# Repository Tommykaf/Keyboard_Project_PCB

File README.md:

# keyboard_project

A Keyboard pcb modeled by @tommykark03, @thunde7, @wifi and @staveyal

## Parts

- MCU: ATMEGA32U4
- USB: TYPE-C-31-M-12
- DIODE: 1N4148W SOD-123

RESISTORS:
- 22 OHM - 0603WAF220JT5E
- 10k OHM - 0603WAF1002T5E
- 5.1K OHM - 0603WAF5101T5E

CAPACITORS:
- 1uF - CL10A105KB8NNNC
- 10uF - CL10A106KP8NNNC 
- 0.1uF (100pF) - CL10C101JB8NNNC

Quartz:
- Yangxing Tech X252016MLD4SC

Tactile reset:
- PANASONIC EVPBB4A9B000

Ferrite Bead:
- GZ1608D601TF

## layout

## MORE SCREENSHOTS

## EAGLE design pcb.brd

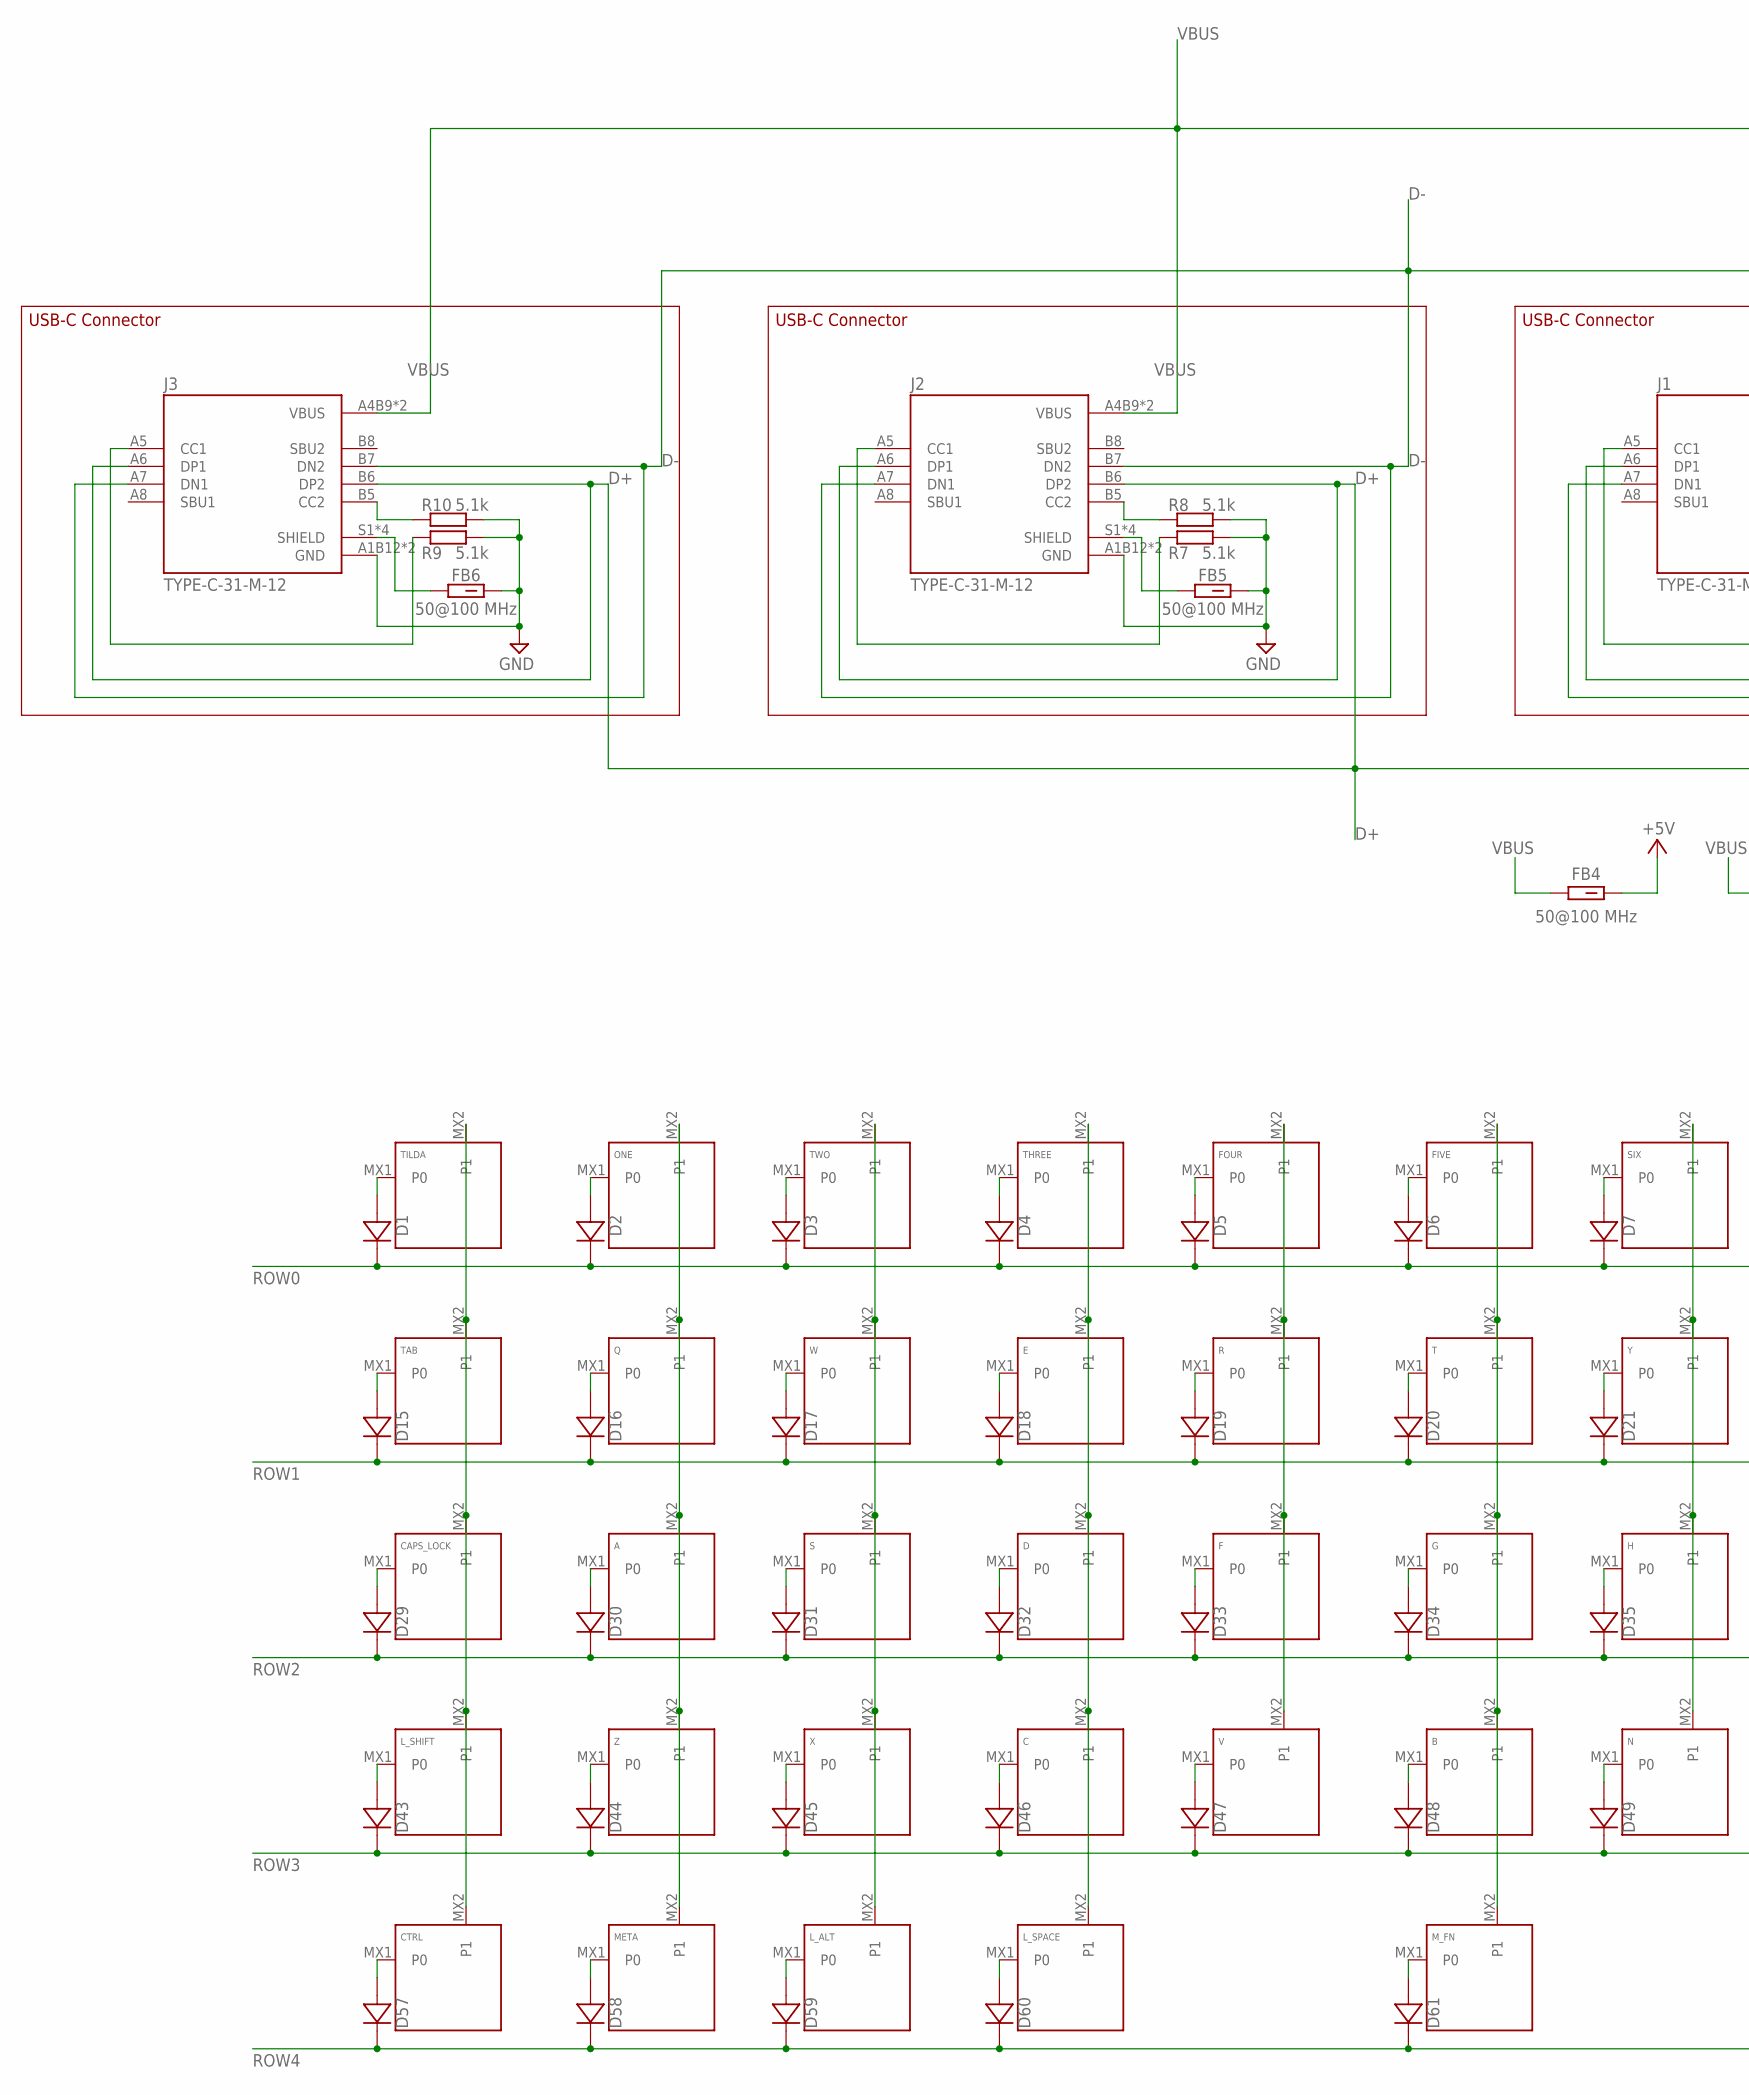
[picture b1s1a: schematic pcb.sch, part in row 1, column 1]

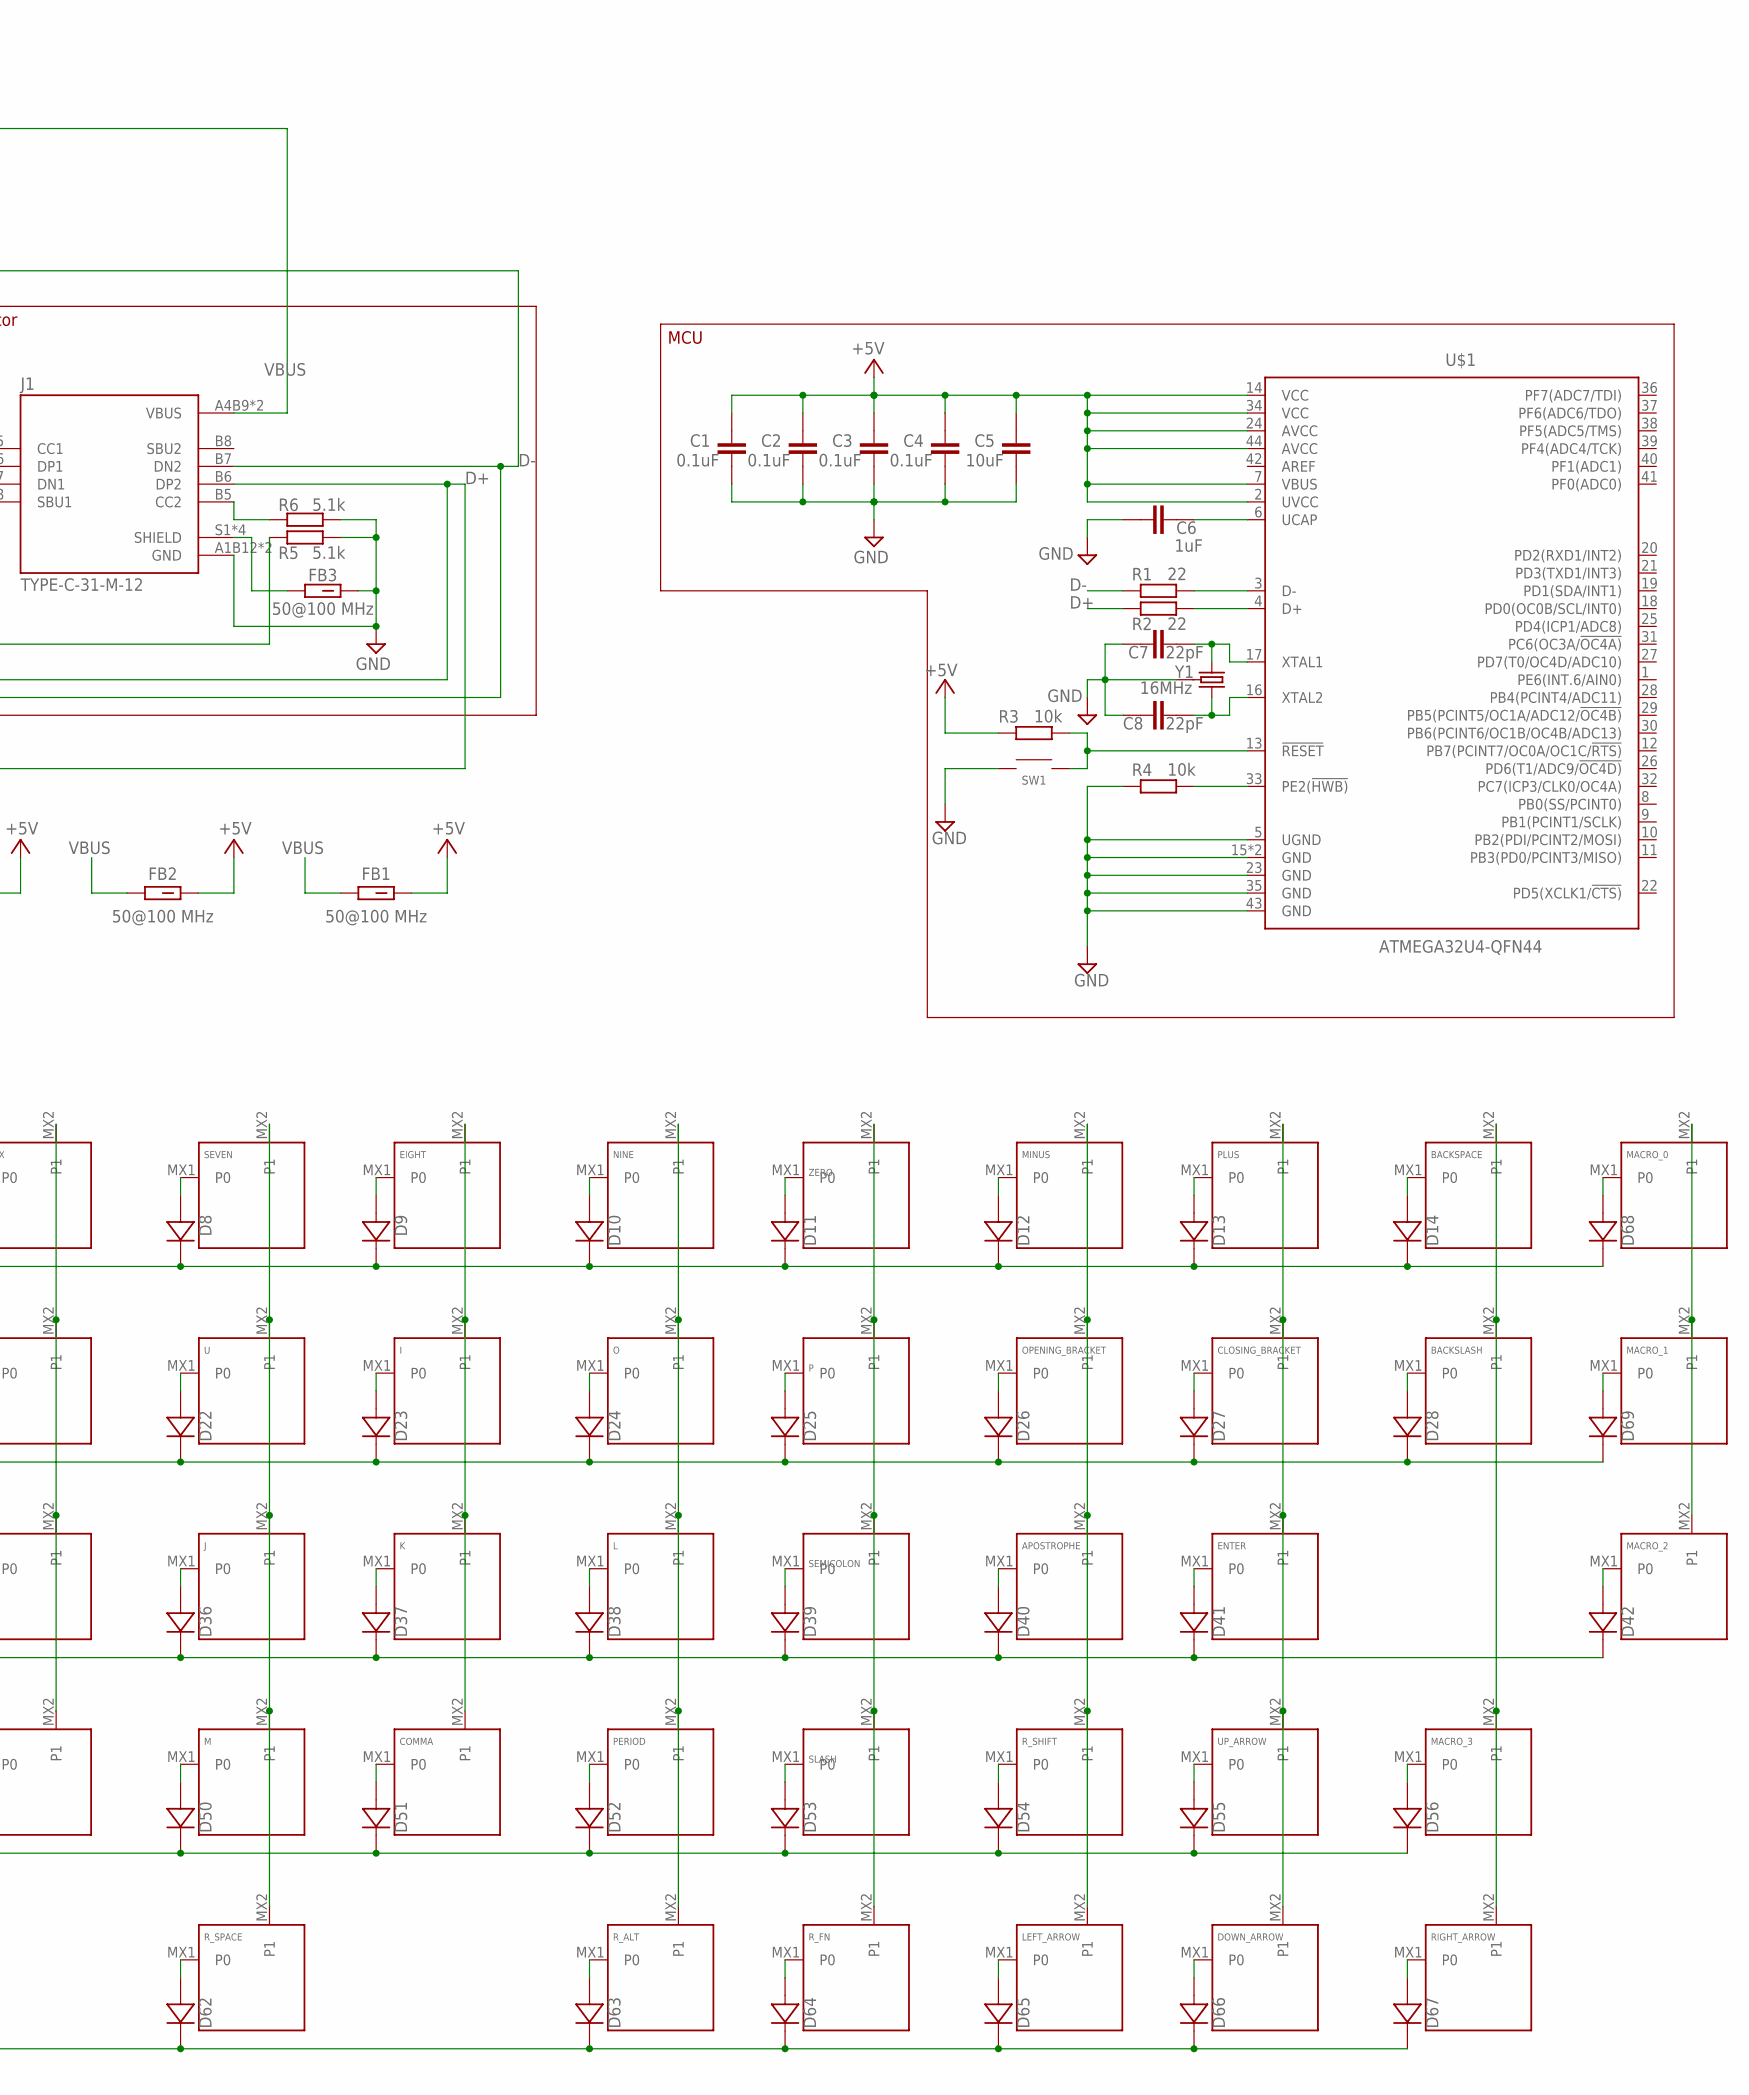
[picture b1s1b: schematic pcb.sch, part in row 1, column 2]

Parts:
A: KEYSWITCH-PLAIN-MXHSPCB-1U; MXHSPCB-1U
APOSTROPHE: KEYSWITCH-PLAIN-MXHSPCB-1U; MXHSPCB-1U
B: KEYSWITCH-PLAIN-MXHSPCB-1U; MXHSPCB-1U
BACKSLASH: KEYSWITCH-PLAIN-MXHSPCB-1U; MXHSPCB-1U
BACKSPACE: KEYSWITCH-PLAIN-MXHSPCB-2U; MXHSPCB-2U
C: KEYSWITCH-PLAIN-MXHSPCB-1U; MXHSPCB-1U
C1, C2, C3, C4: 0.1uF; C0603
C5: 10uF; C0603
C6: 1uF; C0603
C7, C8: 22pF; C0603
CAPS_LOCK: KEYSWITCH-PLAIN-MXHSPCB-1U; MXHSPCB-1U
CLOSING_BRACKET: KEYSWITCH-PLAIN-MXHSPCB-1U; MXHSPCB-1U
COMMA: KEYSWITCH-PLAIN-MXHSPCB-1U; MXHSPCB-1U
CTRL: KEYSWITCH-PLAIN-MXHSPCB-1U; MXHSPCB-1U
D: KEYSWITCH-PLAIN-MXHSPCB-1U; MXHSPCB-1U
D1, D2, D3, D4, D5, D6, D7, D8, D9, D10, D11, D12, D13, D14, D15, D16, D17, D18, D19, D20, D21, D22, D23, D24, D25, D26, D27, D28, D29, D30, D31, D32, D33, D34, D35, D36, D37, D38, D39, D40, D41, D42, D43, D44, D45, D46, D47, D48, D49, D50, D51, D52, D53, D54, D55, D56, D57, D58, D59, D60, D61, D62, D63, D64, D65, D66, D67, D68, D69: DIODE-SOD-123; SOD-123
DOWN_ARROW: KEYSWITCH-PLAIN-MXHSPCB-1U; MXHSPCB-1U
E: KEYSWITCH-PLAIN-MXHSPCB-1U; MXHSPCB-1U
EIGHT: KEYSWITCH-PLAIN-MXHSPCB-1U; MXHSPCB-1U
ENTER: KEYSWITCH-PLAIN-MXHSPCB-2U; MXHSPCB-2U
F: KEYSWITCH-PLAIN-MXHSPCB-1U; MXHSPCB-1U
FB1, FB2, FB3, FB4, FB5, FB6: 50@100 MHz; BEADC1608X95N
FIVE: KEYSWITCH-PLAIN-MXHSPCB-1U; MXHSPCB-1U
FOUR: KEYSWITCH-PLAIN-MXHSPCB-1U; MXHSPCB-1U
G: KEYSWITCH-PLAIN-MXHSPCB-1U; MXHSPCB-1U
H: KEYSWITCH-PLAIN-MXHSPCB-1U; MXHSPCB-1U
I: KEYSWITCH-PLAIN-MXHSPCB-1U; MXHSPCB-1U
J: KEYSWITCH-PLAIN-MXHSPCB-1U; MXHSPCB-1U
J1, J2, J3: TYPE-C-31-M-12; HRO_TYPE-C-31-M-12
K: KEYSWITCH-PLAIN-MXHSPCB-1U; MXHSPCB-1U
L: KEYSWITCH-PLAIN-MXHSPCB-1U; MXHSPCB-1U
LEFT_ARROW: KEYSWITCH-PLAIN-MXHSPCB-1U; MXHSPCB-1U
L_ALT: KEYSWITCH-PLAIN-MXHSPCB-1U; MXHSPCB-1U
L_SHIFT: KEYSWITCH-PLAIN-MXHSPCB-2U; MXHSPCB-2U
L_SPACE: KEYSWITCH-PLAIN-MXHSPCB-2U-FLIPPED; MXHSPCB-2U-FLIPPED
M: KEYSWITCH-PLAIN-MXHSPCB-1U; MXHSPCB-1U
MACRO_0, MACRO_1, MACRO_2, MACRO_3: KEYSWITCH-PLAIN-MXHSPCB-1U; MXHSPCB-1U
META: KEYSWITCH-PLAIN-MXHSPCB-1U; MXHSPCB-1U
MINUS: KEYSWITCH-PLAIN-MXHSPCB-1U; MXHSPCB-1U
M_FN: KEYSWITCH-PLAIN-MXHSPCB-1U; MXHSPCB-1U
N: KEYSWITCH-PLAIN-MXHSPCB-1U; MXHSPCB-1U
NINE: KEYSWITCH-PLAIN-MXHSPCB-1U; MXHSPCB-1U
O: KEYSWITCH-PLAIN-MXHSPCB-1U; MXHSPCB-1U
ONE: KEYSWITCH-PLAIN-MXHSPCB-1U; MXHSPCB-1U
OPENING_BRACKET: KEYSWITCH-PLAIN-MXHSPCB-1U; MXHSPCB-1U
P: KEYSWITCH-PLAIN-MXHSPCB-1U; MXHSPCB-1U
PERIOD: KEYSWITCH-PLAIN-MXHSPCB-1U; MXHSPCB-1U
PLUS: KEYSWITCH-PLAIN-MXHSPCB-1U; MXHSPCB-1U
Q: KEYSWITCH-PLAIN-MXHSPCB-1U; MXHSPCB-1U
R: KEYSWITCH-PLAIN-MXHSPCB-1U; MXHSPCB-1U
R1, R2: 22; R0603
R3, R4: 10k; R0603
R5, R6, R7, R8, R9, R10: 5.1k; R0603
RIGHT_ARROW: KEYSWITCH-PLAIN-MXHSPCB-1U; MXHSPCB-1U
R_ALT: KEYSWITCH-PLAIN-MXHSPCB-1U; MXHSPCB-1U
R_FN: KEYSWITCH-PLAIN-MXHSPCB-1U; MXHSPCB-1U
R_SHIFT: KEYSWITCH-PLAIN-MXHSPCB-1U; MXHSPCB-1U
R_SPACE: KEYSWITCH-PLAIN-MXHSPCB-2U-FLIPPED; MXHSPCB-2U-FLIPPED
S: KEYSWITCH-PLAIN-MXHSPCB-1U; MXHSPCB-1U
SEMICOLON: KEYSWITCH-PLAIN-MXHSPCB-1U; MXHSPCB-1U
SEVEN: KEYSWITCH-PLAIN-MXHSPCB-1U; MXHSPCB-1U
SIX: KEYSWITCH-PLAIN-MXHSPCB-1U; MXHSPCB-1U
SLASH: KEYSWITCH-PLAIN-MXHSPCB-1U; MXHSPCB-1U
SW1: SWITCH-SMD-EVP-BB2A9B00
T: KEYSWITCH-PLAIN-MXHSPCB-1U; MXHSPCB-1U
TAB: KEYSWITCH-PLAIN-MXHSPCB-1U; MXHSPCB-1U
THREE: KEYSWITCH-PLAIN-MXHSPCB-1U; MXHSPCB-1U
TILDA: KEYSWITCH-PLAIN-MXHSPCB-1U; MXHSPCB-1U
TWO: KEYSWITCH-PLAIN-MXHSPCB-1U; MXHSPCB-1U
U: KEYSWITCH-PLAIN-MXHSPCB-1U; MXHSPCB-1U
U$1: ATMEGA32U4-QFN44; QFN-44
UP_ARROW: KEYSWITCH-PLAIN-MXHSPCB-1U; MXHSPCB-1U
V: KEYSWITCH-PLAIN-MXHSPCB-1U; MXHSPCB-1U
W: KEYSWITCH-PLAIN-MXHSPCB-1U; MXHSPCB-1U
X: KEYSWITCH-PLAIN-MXHSPCB-1U; MXHSPCB-1U
Y: KEYSWITCH-PLAIN-MXHSPCB-1U; MXHSPCB-1U
Y1: 16MHz; CRYSTAL-SMD-2X2.5MM
Z: KEYSWITCH-PLAIN-MXHSPCB-1U; MXHSPCB-1U
ZERO: KEYSWITCH-PLAIN-MXHSPCB-1U; MXHSPCB-1U

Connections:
+5V: FB1.2, FB2.2, FB4.2
D+: J1.A6 (DP1), J1.B6 (DP2), J2.A6 (DP1), J2.B6 (DP2), J3.A6 (DP1), J3.B6 (DP2), R2.1
D-: J1.A7 (DN1), J1.B7 (DN2), J2.A7 (DN1), J2.B7 (DN2), J3.A7 (DN1), J3.B7 (DN2), R1.1
GND: C1.1, C2.1, C3.1, C4.1, C5.1, C6.1, C7.1, C8.1, FB3.2, FB5.2, FB6.2, J1.A1B12 (GND), J1.B1A12 (GND), J2.A1B12 (GND), J2.B1A12 (GND), J3.A1B12 (GND), J3.B1A12 (GND), R4.1, R5.2, R6.2, R7.2, R8.2, R9.2, R10.2, SW1.A@1 (1), SW1.A@2 (1), U$1.5 (UGND), U$1.15 (GND), U$1.23 (GND), U$1.35 (GND), U$1.43 (GND), U$1.TAB (GND), Y1.P2 (GND), Y1.P4 (GND)
unnamed: D1.A, TILDA.MX1 (P0)
unnamed: D2.A, ONE.MX1 (P0)
unnamed: D3.A, TWO.MX1 (P0)
unnamed: D4.A, THREE.MX1 (P0)
unnamed: D5.A, FOUR.MX1 (P0)
unnamed: D6.A, FIVE.MX1 (P0)
unnamed: D7.A, SIX.MX1 (P0)
unnamed: D8.A, SEVEN.MX1 (P0)
unnamed: D9.A, EIGHT.MX1 (P0)
unnamed: D10.A, NINE.MX1 (P0)
unnamed: D11.A, ZERO.MX1 (P0)
unnamed: D12.A, MINUS.MX1 (P0)
unnamed: D13.A, PLUS.MX1 (P0)
unnamed: BACKSPACE.MX1 (P0), D14.A
unnamed: D15.A, TAB.MX1 (P0)
unnamed: D16.A, Q.MX1 (P0)
unnamed: D17.A, W.MX1 (P0)
unnamed: D18.A, E.MX1 (P0)
unnamed: D19.A, R.MX1 (P0)
unnamed: D20.A, T.MX1 (P0)
unnamed: D21.A, Y.MX1 (P0)
unnamed: D22.A, U.MX1 (P0)
unnamed: D23.A, I.MX1 (P0)
unnamed: D24.A, O.MX1 (P0)
unnamed: D25.A, P.MX1 (P0)
unnamed: D26.A, OPENING_BRACKET.MX1 (P0)
unnamed: CLOSING_BRACKET.MX1 (P0), D27.A
unnamed: BACKSLASH.MX1 (P0), D28.A
unnamed: CAPS_LOCK.MX1 (P0), D29.A
unnamed: A.MX1 (P0), D30.A
unnamed: D31.A, S.MX1 (P0)
unnamed: D.MX1 (P0), D32.A
unnamed: D33.A, F.MX1 (P0)
unnamed: D34.A, G.MX1 (P0)
unnamed: D35.A, H.MX1 (P0)
unnamed: D36.A, J.MX1 (P0)
unnamed: D37.A, K.MX1 (P0)
unnamed: D38.A, L.MX1 (P0)
unnamed: D39.A, SEMICOLON.MX1 (P0)
unnamed: APOSTROPHE.MX1 (P0), D40.A
unnamed: D41.A, ENTER.MX1 (P0)
unnamed: D42.A, MACRO_2.MX1 (P0)
unnamed: D43.A, L_SHIFT.MX1 (P0)
unnamed: D44.A, Z.MX1 (P0)
unnamed: D45.A, X.MX1 (P0)
unnamed: C.MX1 (P0), D46.A
unnamed: D47.A, V.MX1 (P0)
unnamed: B.MX1 (P0), D48.A
unnamed: D49.A, N.MX1 (P0)
unnamed: D50.A, M.MX1 (P0)
unnamed: COMMA.MX1 (P0), D51.A
unnamed: D52.A, PERIOD.MX1 (P0)
unnamed: D53.A, SLASH.MX1 (P0)
unnamed: D54.A, R_SHIFT.MX1 (P0)
unnamed: D55.A, UP_ARROW.MX1 (P0)
unnamed: D56.A, MACRO_3.MX1 (P0)
unnamed: CTRL.MX1 (P0), D57.A
unnamed: D58.A, META.MX1 (P0)
unnamed: D59.A, L_ALT.MX1 (P0)
unnamed: D60.A, L_SPACE.MX1 (P0)
unnamed: D62.A, R_SPACE.MX1 (P0)
unnamed: D63.A, R_ALT.MX1 (P0)
unnamed: D65.A, LEFT_ARROW.MX1 (P0)
unnamed: D67.A, RIGHT_ARROW.MX1 (P0)
unnamed: D69.A, MACRO_1.MX1 (P0)
unnamed: D68.A, MACRO_0.MX1 (P0)
unnamed: D61.A, M_FN.MX1 (P0)
unnamed: D66.A, DOWN_ARROW.MX1 (P0)
unnamed: D64.A, R_FN.MX1 (P0)
unnamed: CAPS_LOCK.MX2 (P1), CTRL.MX2 (P1), L_SHIFT.MX2 (P1), TAB.MX2 (P1), TILDA.MX2 (P1)
unnamed: A.MX2 (P1), META.MX2 (P1), ONE.MX2 (P1), Q.MX2 (P1), Z.MX2 (P1)
unnamed: L_ALT.MX2 (P1), S.MX2 (P1), TWO.MX2 (P1), W.MX2 (P1), X.MX2 (P1)
unnamed: C.MX2 (P1), D.MX2 (P1), E.MX2 (P1), L_SPACE.MX2 (P1), THREE.MX2 (P1)
unnamed: F.MX2 (P1), FOUR.MX2 (P1), R.MX2 (P1), V.MX2 (P1)
unnamed: B.MX2 (P1), FIVE.MX2 (P1), G.MX2 (P1), M_FN.MX2 (P1), T.MX2 (P1)
unnamed: H.MX2 (P1), N.MX2 (P1), SIX.MX2 (P1), Y.MX2 (P1)
unnamed: J.MX2 (P1), M.MX2 (P1), R_SPACE.MX2 (P1), SEVEN.MX2 (P1), U.MX2 (P1)
unnamed: COMMA.MX2 (P1), EIGHT.MX2 (P1), I.MX2 (P1), K.MX2 (P1)
unnamed: L.MX2 (P1), NINE.MX2 (P1), O.MX2 (P1), PERIOD.MX2 (P1), R_ALT.MX2 (P1)
unnamed: APOSTROPHE.MX2 (P1), LEFT_ARROW.MX2 (P1), MINUS.MX2 (P1), OPENING_BRACKET.MX2 (P1), R_SHIFT.MX2 (P1)
unnamed: P.MX2 (P1), R_FN.MX2 (P1), SEMICOLON.MX2 (P1), SLASH.MX2 (P1), ZERO.MX2 (P1)
unnamed: CLOSING_BRACKET.MX2 (P1), DOWN_ARROW.MX2 (P1), ENTER.MX2 (P1), PLUS.MX2 (P1), UP_ARROW.MX2 (P1)
unnamed: BACKSLASH.MX2 (P1), BACKSPACE.MX2 (P1), MACRO_3.MX2 (P1), RIGHT_ARROW.MX2 (P1)
unnamed: MACRO_0.MX2 (P1), MACRO_1.MX2 (P1), MACRO_2.MX2 (P1)
unnamed: R4.2, U$1.33 (PE2(!HWB))
unnamed: R3.2, SW1.B@3 (2), SW1.B@4 (2), U$1.13 (!RESET)
unnamed: C7.2, U$1.17 (XTAL1), Y1.P1 (1)
unnamed: C8.2, U$1.16 (XTAL2), Y1.P3 (2)
unnamed: R2.2, U$1.4 (D+)
unnamed: R1.2, U$1.3 (D-)
unnamed: C6.2, U$1.6 (UCAP)
unnamed: J2.A5 (CC1), R7.1
unnamed: J1.A5 (CC1), R5.1
unnamed: J1.B5 (CC2), R6.1
unnamed: J2.B5 (CC2), R8.1
unnamed: FB5.1, J2.S1 (SHIELD), J2.S2 (SHIELD), J2.S3 (SHIELD), J2.S4 (SHIELD)
unnamed: J3.A5 (CC1), R9.1
unnamed: FB3.1, J1.S1 (SHIELD), J1.S2 (SHIELD), J1.S3 (SHIELD), J1.S4 (SHIELD)
unnamed: J3.B5 (CC2), R10.1
unnamed: FB6.1, J3.S1 (SHIELD), J3.S2 (SHIELD), J3.S3 (SHIELD), J3.S4 (SHIELD)
ROW0: D1.C, D2.C, D3.C, D4.C, D5.C, D6.C, D7.C, D8.C, D9.C, D10.C, D11.C, D12.C, D13.C, D14.C, D68.C
ROW1: D15.C, D16.C, D17.C, D18.C, D19.C, D20.C, D21.C, D22.C, D23.C, D24.C, D25.C, D26.C, D27.C, D28.C, D69.C
ROW2: D29.C, D30.C, D31.C, D32.C, D33.C, D34.C, D35.C, D36.C, D37.C, D38.C, D39.C, D40.C, D41.C, D42.C
ROW3: D43.C, D44.C, D45.C, D46.C, D47.C, D48.C, D49.C, D50.C, D51.C, D52.C, D53.C, D54.C, D55.C, D56.C
ROW4: D57.C, D58.C, D59.C, D60.C, D61.C, D62.C, D63.C, D64.C, D65.C, D66.C, D67.C
VBUS: FB1.1, FB2.1, FB4.1, J1.A4B9 (VBUS), J1.B4A9 (VBUS), J2.A4B9 (VBUS), J2.B4A9 (VBUS), J3.A4B9 (VBUS), J3.B4A9 (VBUS)
VCC: C1.2, C2.2, C3.2, C4.2, C5.2, R3.1, U$1.2 (UVCC), U$1.7 (VBUS), U$1.14 (VCC), U$1.24 (AVCC), U$1.34 (VCC), U$1.44 (AVCC)

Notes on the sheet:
USB-C Connector
MCU

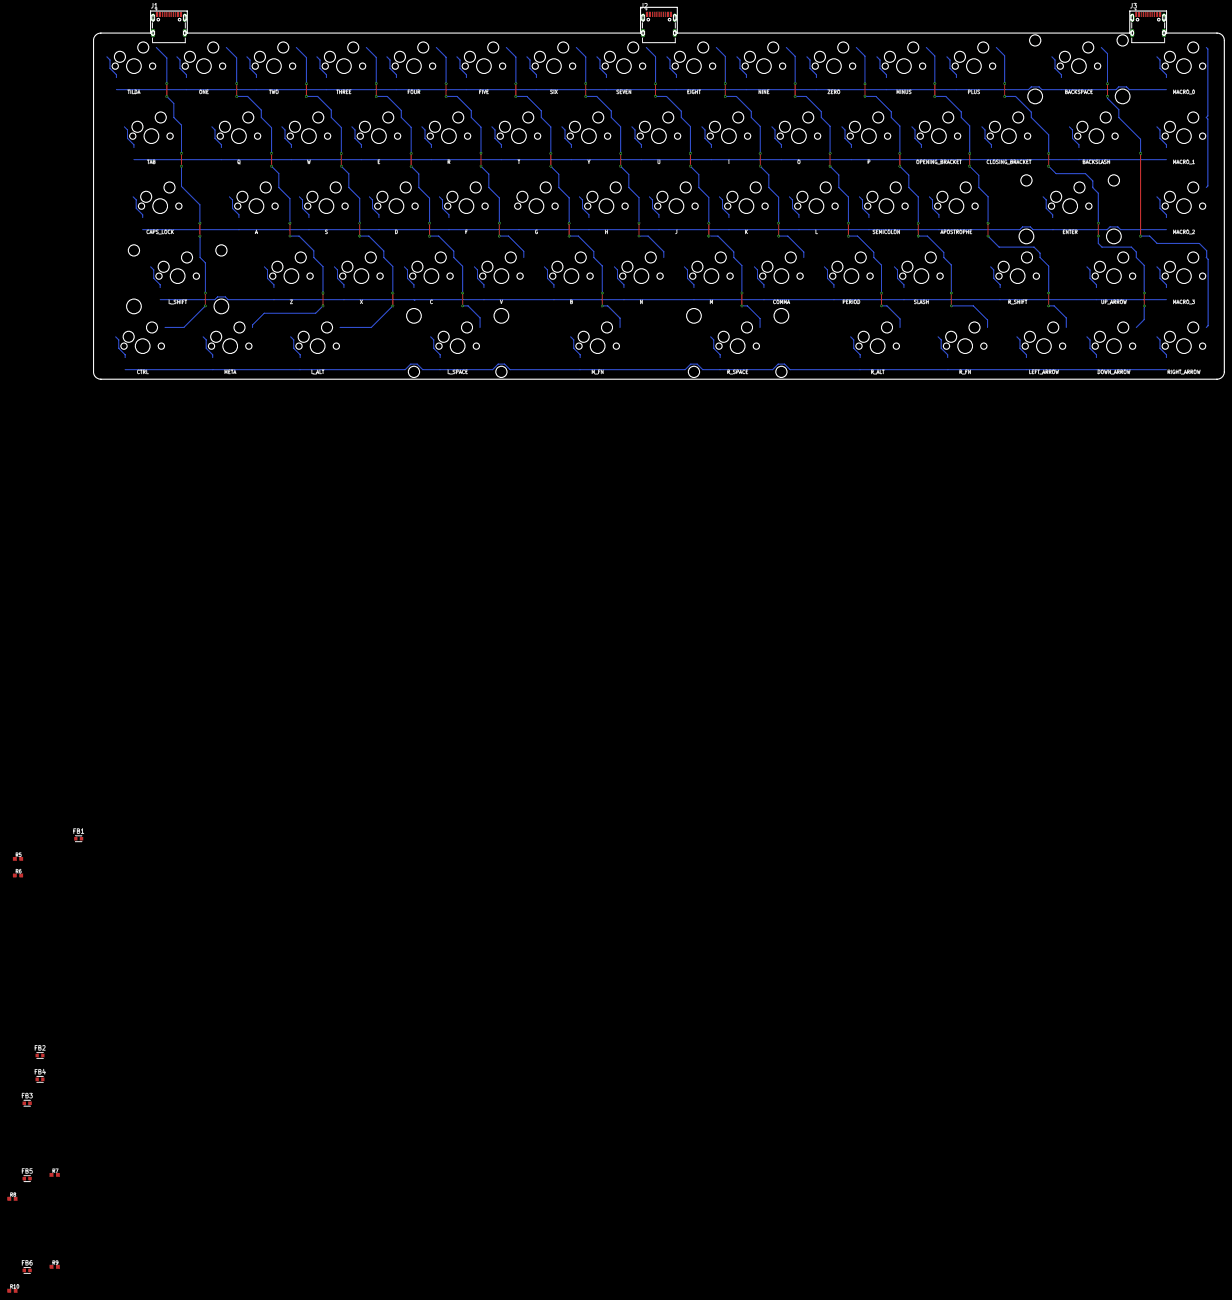
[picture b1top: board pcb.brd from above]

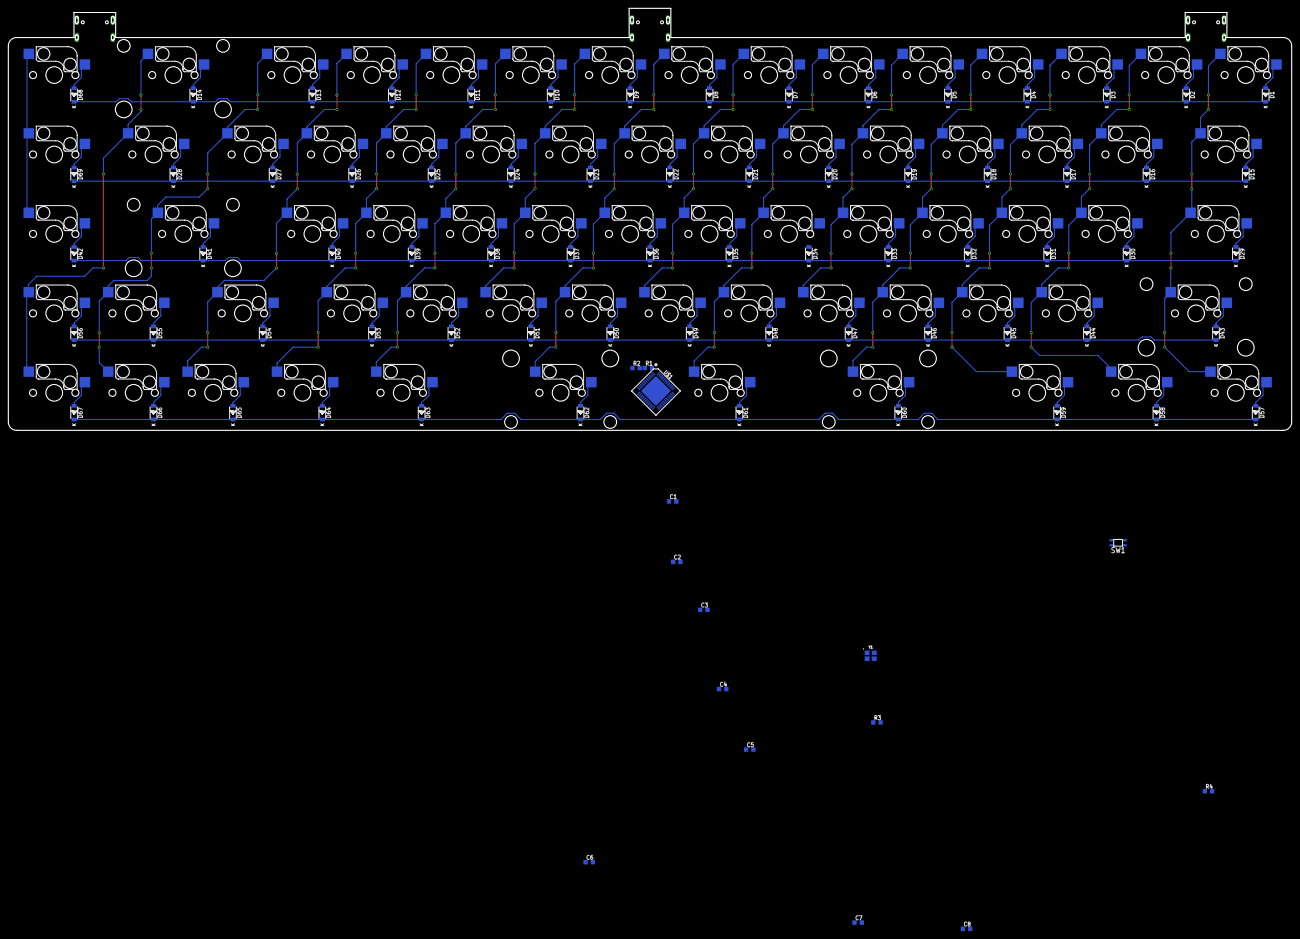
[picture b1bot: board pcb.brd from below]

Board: 2 copper layers, 307.8 x 101.2 mm, 168 parts (153 on the bottom side), 111 nets.

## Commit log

2021-02-19 inital commit - added switches, diodes, etc...
2021-02-19 added gitignore
2021-02-19 removed stray net
2021-02-20 updated matrix and streched pcb
2021-03-02 added MCU scheme + readme
2021-03-03 added USB-C + ferrite beads

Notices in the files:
parts and their libraries:
SparkFun-Clocks: Licensing: Creative Commons ShareAlike 4.0 International - https://creativecommons.org/licenses/by-sa/4.0
